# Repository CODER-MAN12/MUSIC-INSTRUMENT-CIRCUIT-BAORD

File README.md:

[README.md](https://github.com/user-attachments/files/33922701/README.md)
 Project Status: Under Active Development. This device currently has no firmware installed. It is an unprogrammed hardware shell that cannot communicate with your computer or music software out of the box yet.
 
A custom-designed, programmable mechanical keyboard featuring an ergonomic layout, onboard USB-C connectivity, and full-custom PCB architecture designed in KiCad.   📋 Table of ContentsOverviewFeaturesHardware Architecture & LayoutBill of Materials (BOM)Repository StructureBuilding & Assembly InstructionsFirmware SetupLicense🔍 OverviewThe [Project Name] is an open-source hardware project built from scratch to provide a reliable, sleek, and fully programmable input device. As visualized in the KiCad 3D viewer, the board integrates MX-style mechanical switches, surface-mount diodes, and a clean USB-C interface for modern compatibility.   Whether you are looking to streamline your daily workflow, optimize gaming macros, or dive into custom keyboard design, this repository contains everything you need to manufacture, assemble, and flash your own board.✨

FeaturesModern Connectivity: Reversible or standard Type-C USB port implementation for power and data transmission.   Mechanical Switch Support: Compatible with standard 3-pin and 5-pin MX-style mechanical switches.   Compact & Ergonomic: Optimized layout designed for minimal desk footprint and maximum efficiency.Open-Source Hardware: Fully editable KiCad schematic and PCB files allowing for easy customization and forks.Firmware Ready: Compatible with popular custom keyboard firmware ecosystems (e.g., QMK, VIA, or KMK).📐 Hardware Architecture & LayoutThe PCB design features:Microcontroller: [e.g., ATmega32U4 / RP2040 / STM32] handling USB communication and matrix scanning.Switch Matrix: Designed with individual switching diodes to prevent ghosting during multi-key rollover (NKRO).Low-Profile Integration: Compact component placement to maintain a low profile inside custom 3D-printed or CNC-machined cases.

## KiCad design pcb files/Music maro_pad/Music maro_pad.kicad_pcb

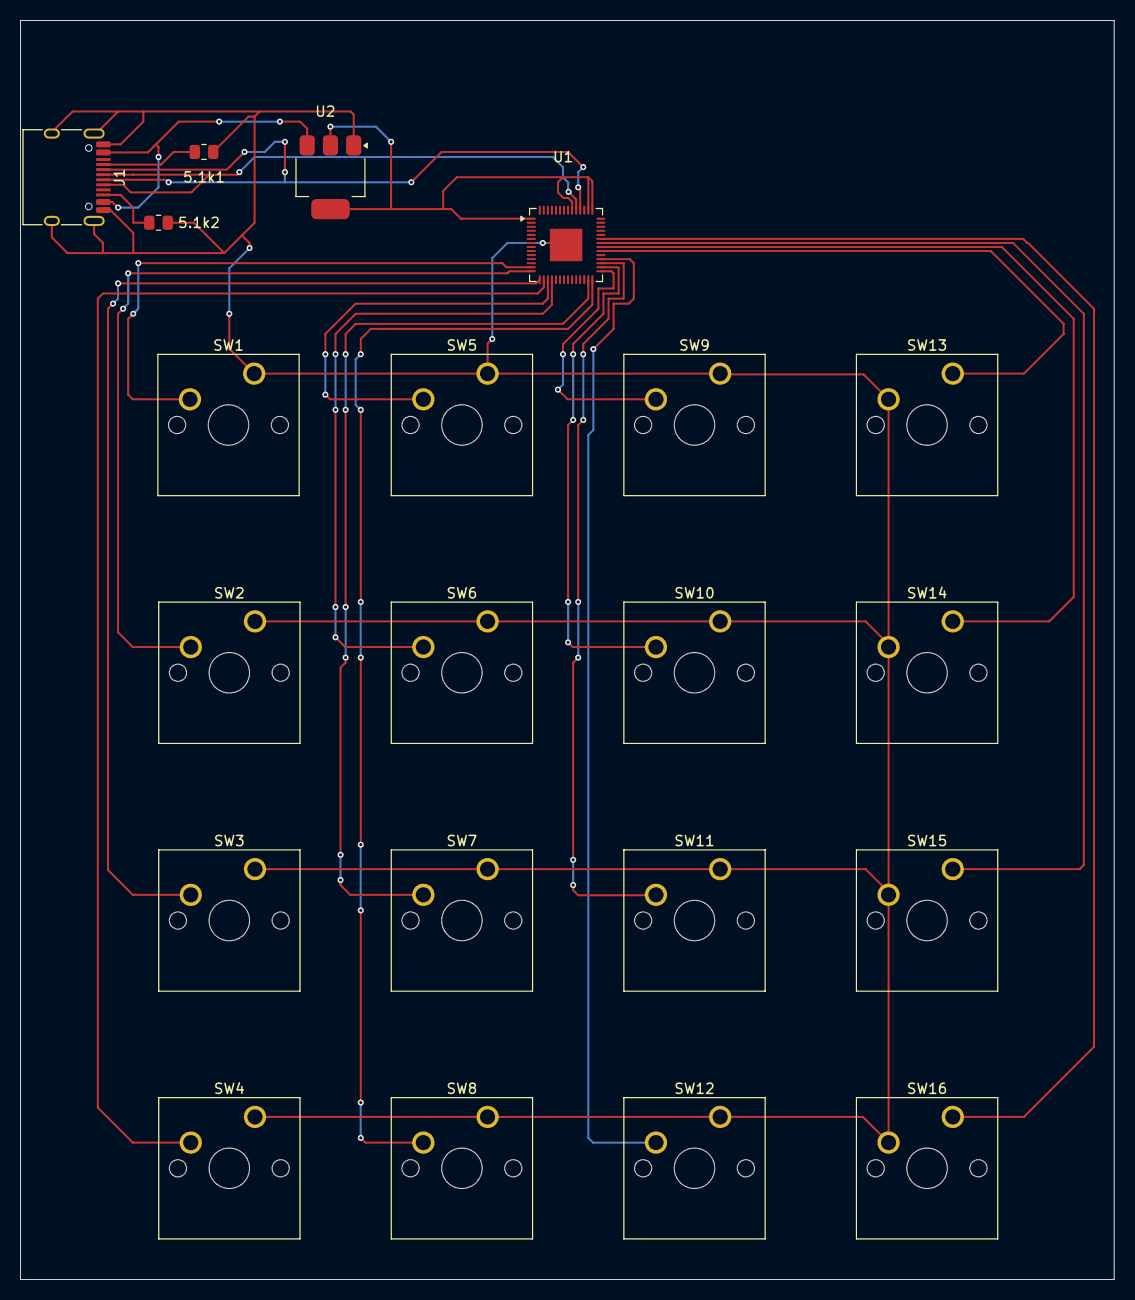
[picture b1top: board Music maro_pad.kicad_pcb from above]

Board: 2 copper layers, 108.2 x 124.5 mm, 21 parts (0 on the bottom side), 23 nets.

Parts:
5.1k1, 5.1k2: 5.1kΩ; R_0805_2012Metric
J1: USB_C_Receptacle_USB2.0_16P; USB_C_Receptacle_HRO_TYPE-C-31-M-12
SW1, SW2, SW3, SW4, SW5, SW6, SW7, SW8, SW9, SW10, SW11, SW12, SW13, SW14, SW15, SW16: SW_Push; SW_Cherry_MX_1.00u_PCB
U1: RP2040; QFN-56-1EP_7x7mm_P0.4mm_EP3.2x3.2mm
U2: LD1117S33TR_SOT223; SOT-223-3_TabPin2

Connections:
unnamed: 5.1k1.1, J1.A5 (CC1)
unnamed: 5.1k2.1, J1.B5 (CC2)
unnamed: 5.1k1.2, 5.1k2.2, J1.A1 (GND), J1.A12 (GND), J1.B1 (GND), J1.B12 (GND), J1.SH (SHIELD), SW1.1, SW2.1, SW3.1, SW4.1, SW5.1, SW6.1, SW7.1, SW8.1, SW9.1, SW10.1, SW11.1, SW12.1, SW13.2, SW14.2, SW15.2, SW16.2, U1.57 (GND), U2.1 (GND)
unnamed: U1.1 (IOVDD), U1.43 (ADC_AVDD), U1.44 (VREG_VIN), U1.48 (USB_VDD), U2.2 (VO)
unnamed: SW1.2, U1.13 (GPIO10)
unnamed: SW2.2, U1.14 (GPIO11)
unnamed: SW3.2, U1.15 (GPIO12)
unnamed: SW4.2, U1.16 (GPIO13)
unnamed: SW5.2, U1.17 (GPIO14)
unnamed: SW6.2, U1.18 (GPIO15)
unnamed: SW7.2, U1.27 (GPIO16)
unnamed: SW8.2, U1.28 (GPIO17)
unnamed: SW9.2, U1.29 (GPIO18)
unnamed: SW10.2, U1.30 (GPIO19)
unnamed: SW11.2, U1.31 (GPIO20)
unnamed: SW12.2, U1.32 (GPIO21)
unnamed: SW13.1, U1.34 (GPIO22)
unnamed: SW14.1, U1.35 (GPIO23)
unnamed: SW15.1, U1.36 (GPIO24)
unnamed: SW16.1, U1.37 (GPIO25)
unnamed: J1.A7 (D-), J1.B7 (D-), U1.46 (USB_DM)
unnamed: J1.A6 (D+), J1.B6 (D+), U1.47 (USB_DP)
unnamed: J1.A4 (VBUS), J1.A9 (VBUS), J1.B4 (VBUS), J1.B9 (VBUS), U2.3 (VI)

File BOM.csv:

Item,Qty,Supplier,Cost/item,Total Cost,link
5.1kΩ,2,,$0.01,$0.02,
USB_C_Receptacle_USB2.0_16P,1,,$0.35,$0.35,
Blue Mechanical Switch,16,,$0.45,$7.20,
RP2040,1,,$0.92,$0.92,
LD1117S33TR_SOT223,1,,$0.25,$0.25,
Pcd-way,1,PCB-way,$55.00,$55.00,https://www.pcbway.com/
Estimated total shipping,1,,,$0.00,
